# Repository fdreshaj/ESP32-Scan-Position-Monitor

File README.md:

Work in Progress, RF branch for RF. Will be updating with new design

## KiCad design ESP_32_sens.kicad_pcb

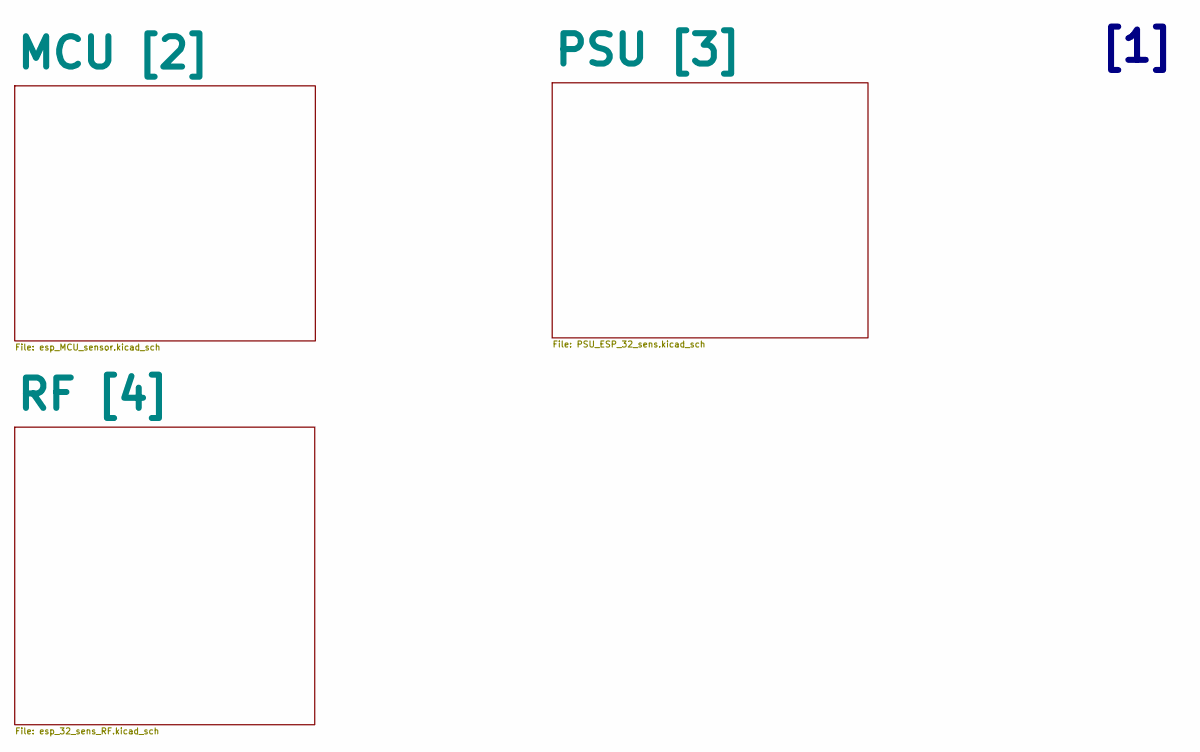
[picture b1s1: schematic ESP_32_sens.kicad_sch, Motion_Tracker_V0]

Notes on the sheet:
[1]

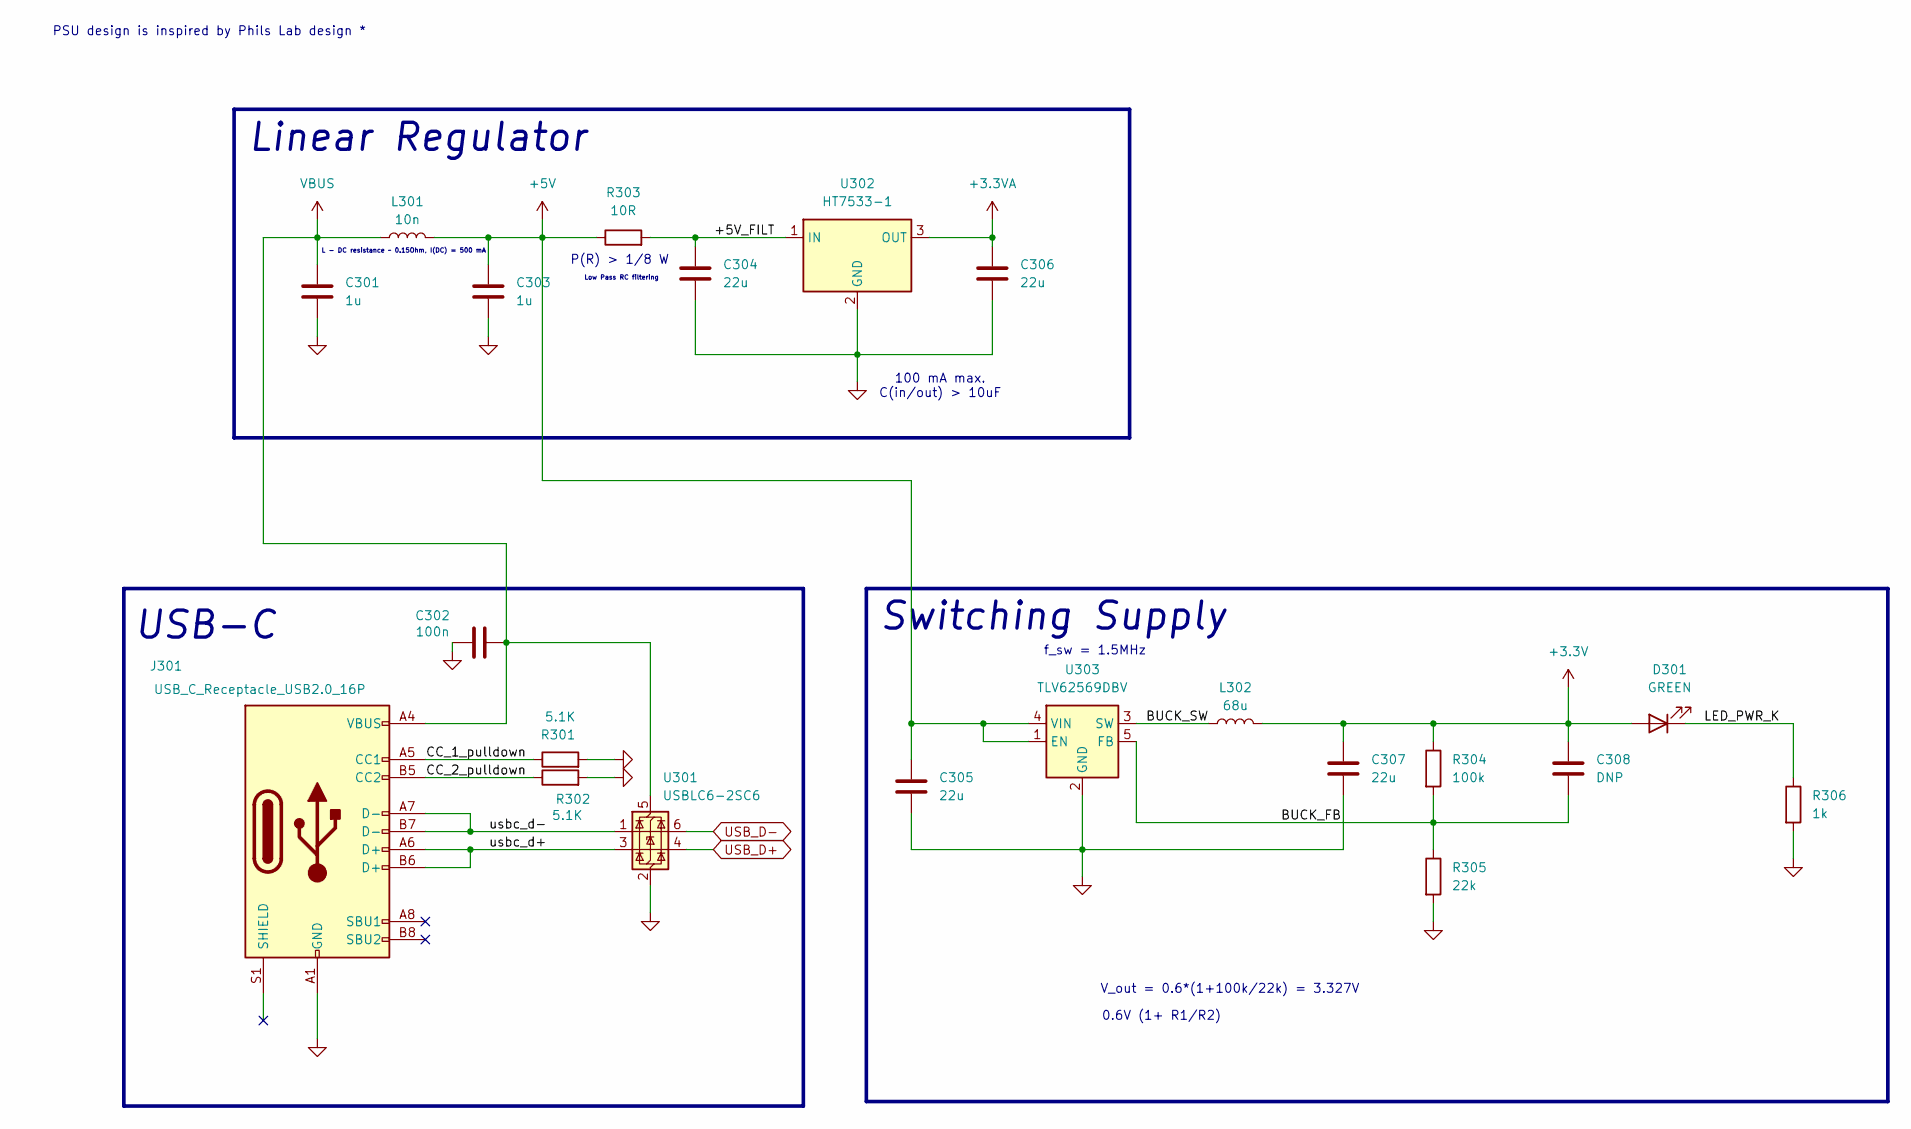
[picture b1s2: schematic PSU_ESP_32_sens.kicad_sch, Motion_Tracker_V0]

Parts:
C301, C303: 1u; C_0603_1608Metric_Pad1.08x0.95mm_HandSolder
C302: 100n; C_0402_1005Metric_Pad0.74x0.62mm_HandSolder
C304, C305, C306, C307: 22u; C_0603_1608Metric_Pad1.08x0.95mm_HandSolder
C308: DNP; C_0402_1005Metric_Pad0.74x0.62mm_HandSolder
D301: GREEN; LED_0402_1005Metric_Pad0.77x0.64mm_HandSolder
J301: USB_C_Receptacle_USB2.0_16P; USB_C_Receptacle_G-Switch_GT-USB-7010ASV
L301: 10n; L_0402_1005Metric_Pad0.77x0.64mm_HandSolder
L302: 68u; L_0603_1608Metric_Pad1.05x0.95mm_HandSolder
R301, R302: 5.1K; R_0402_1005Metric_Pad0.72x0.64mm_HandSolder
R303: 10R; R_0402_1005Metric_Pad0.72x0.64mm_HandSolder
R304: 100k; R_0402_1005Metric_Pad0.72x0.64mm_HandSolder
R305: 22k; R_0402_1005Metric_Pad0.72x0.64mm_HandSolder
R306: 1k; R_0402_1005Metric_Pad0.72x0.64mm_HandSolder
U301: USBLC6-2SC6; SOT-23-6
U302: HT7533-1; SOT-223-3_TabPin2
U303: TLV62569DBV; SOT-23-5

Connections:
+3.3V: C307.1, C308.1, D301.2 (A), L302.2, R304.1; also elsewhere on the board
+3.3VA: C306.1, U302.3 (OUT); also elsewhere on the board
+5V: C303.1, C305.1, L301.2, R303.1, U303.1 (EN), U303.4 (VIN)
/PSU [3]/+5V_FILT: C304.1, R303.2, U302.1 (IN)
/PSU [3]/BUCK_FB: C308.2, R304.2, R305.1, U303.5 (FB)
/PSU [3]/BUCK_SW: L302.1, U303.3 (SW)
/PSU [3]/CC_1_pulldown: J301.A5 (CC1), R301.1
/PSU [3]/CC_2_pulldown: J301.B5 (CC2), R302.1
/PSU [3]/LED_PWR_K: D301.1 (K), R306.1
/PSU [3]/usbc_d+: J301.A6 (D+), J301.B6 (D+), U301.3 (I/O2)
/PSU [3]/usbc_d-: J301.A7 (D-), J301.B7 (D-), U301.1 (I/O1)
GND: C301.2, C302.1, C303.2, C304.2, C305.2, C306.2, C307.2, J301.A1 (GND), J301.A12 (GND), J301.B1 (GND), J301.B12 (GND), R301.2, R302.2, R305.2, R306.2, U301.2 (GND), U302.2 (GND), U303.2 (GND); also elsewhere on the board
USB_D+: U301.4 (I/O2); also elsewhere on the board
USB_D-: U301.6 (I/O1); also elsewhere on the board
VBUS: C301.1, C302.2, J301.A4 (VBUS), J301.A9 (VBUS), J301.B4 (VBUS), J301.B9 (VBUS), L301.1, U301.5 (VBUS)

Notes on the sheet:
USB-C
Linear Regulator
V_out = 0.6*(1+100k/22k) = 3.327V
Low Pass RC filtering
0.6V (1+ R1/R2)
f_sw = 1.5MHz
Switching Supply
L - DC resistance ~ 0.15Ohm, I(DC) = 500 mA
P(R) > 1/8 W
100 mA max. C(in/out) > 10uF
PSU design is inspired by Phils Lab design *

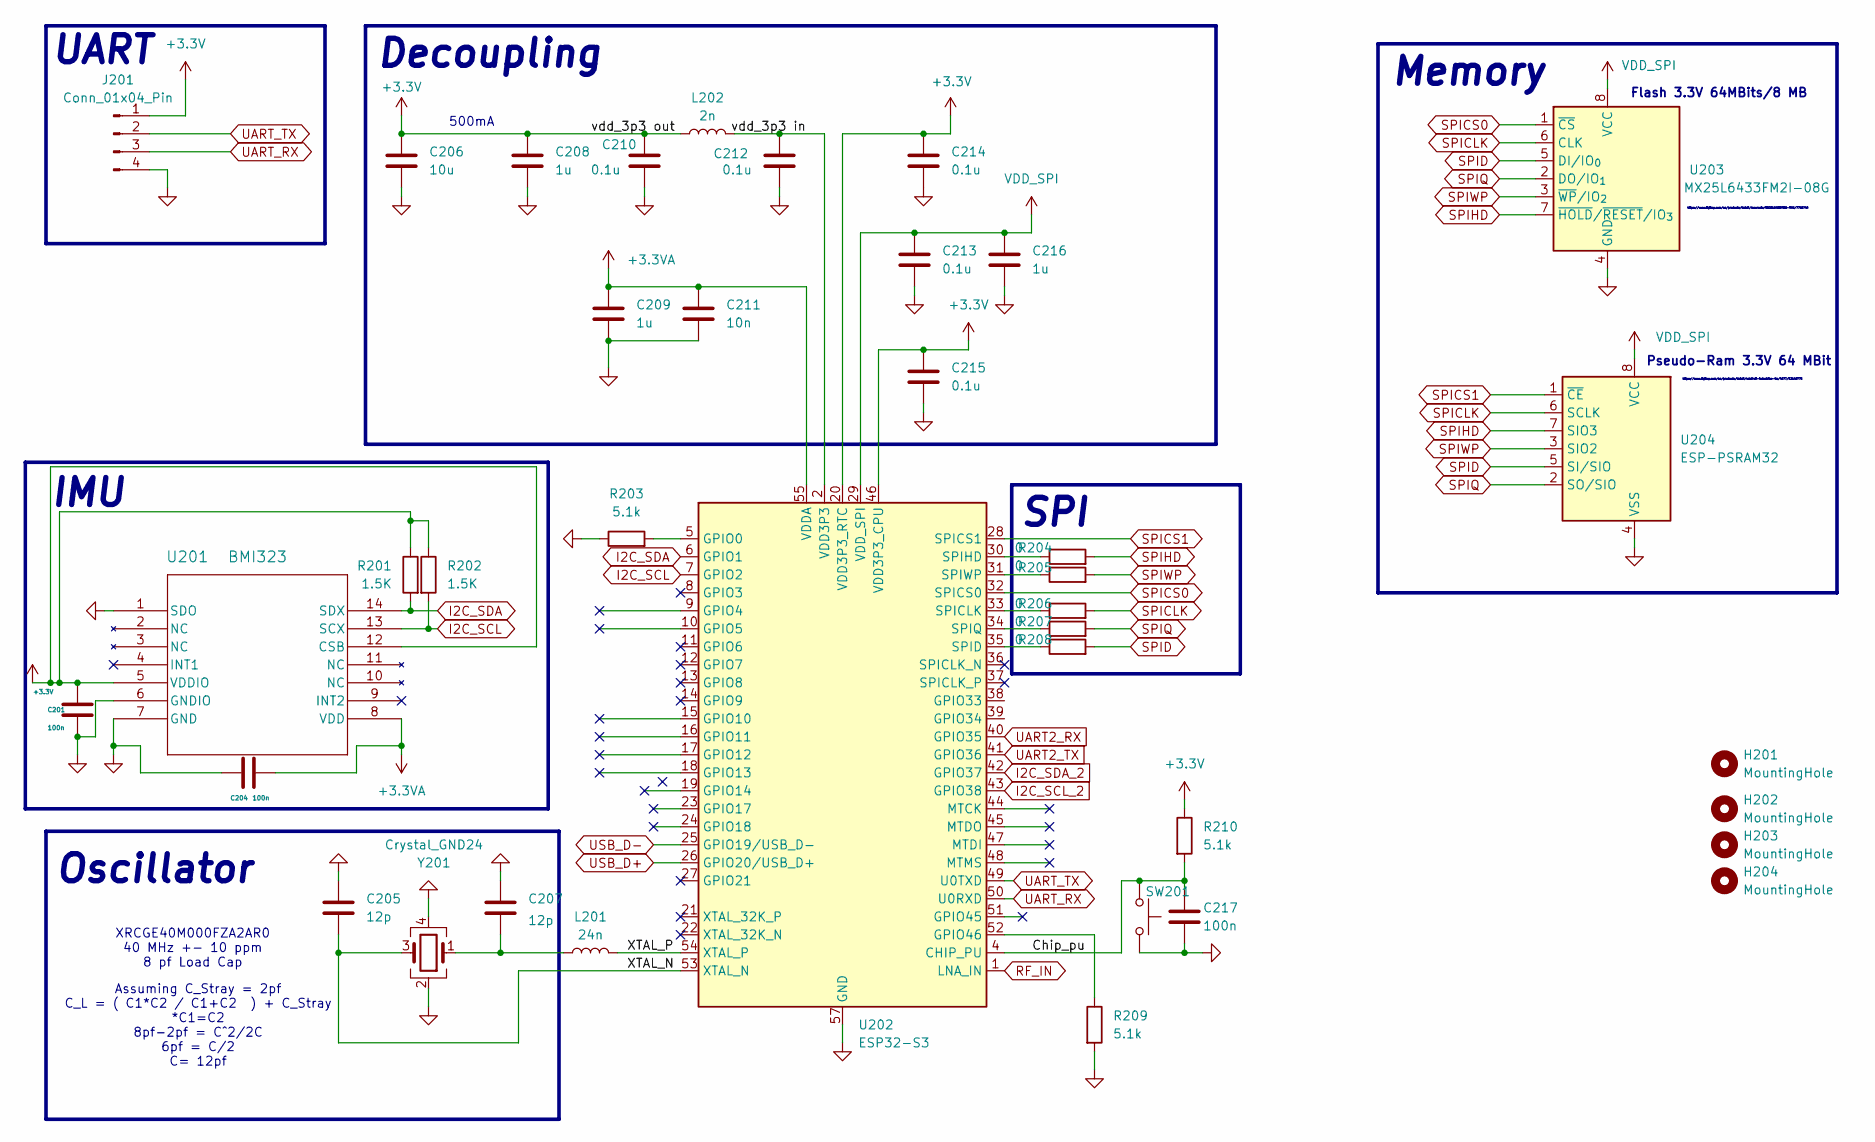
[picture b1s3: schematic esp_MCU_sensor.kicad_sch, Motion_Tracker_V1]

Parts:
C201, C204, C217: 100n; C_0402_1005Metric_Pad0.74x0.62mm_HandSolder
C205, C207: 12p; C_0402_1005Metric_Pad0.74x0.62mm_HandSolder
C206: 10u; C_0603_1608Metric_Pad1.08x0.95mm_HandSolder
C208, C209, C216: 1u; C_0603_1608Metric_Pad1.08x0.95mm_HandSolder
C210, C212, C213, C214, C215: 0.1u; C_0402_1005Metric_Pad0.74x0.62mm_HandSolder
C211: 10n; C_0402_1005Metric_Pad0.74x0.62mm_HandSolder
H201, H202, H203, H204: MountingHole; MountingHole_3.2mm_M3
J201: Conn_01x04_Pin; Wuerth_WR-WTB_64800411622_1x04_P1.50mm_Vertical
L201: 24n; L_0402_1005Metric_Pad0.77x0.64mm_HandSolder
L202: 2n; L_0402_1005Metric_Pad0.77x0.64mm_HandSolder
R201, R202: 1.5K; R_0402_1005Metric_Pad0.72x0.64mm_HandSolder
R203, R209, R210: 5.1k; R_0402_1005Metric_Pad0.72x0.64mm_HandSolder
R204, R205, R206, R207, R208: 0; R_0402_1005Metric_Pad0.72x0.64mm_HandSolder
SW201: SW_Push; SW_PUSH_6mm_H4.3mm
U201: BMI323; BMI323_BOS
U202: ESP32-S3; QFN-56-1EP_7x7mm_P0.4mm_EP4x4mm
U203: MX25L6433FM2I-08G; SOIC-8_5.3x5.3mm_P1.27mm
U204: ESP-PSRAM32; SOIC-8_3.9x4.9mm_P1.27mm
Y201: Crystal_GND24; Crystal_SMD_SeikoEpson_FA128-4Pin_2.0x1.6mm

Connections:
+3.3V: C201.1, C206.2, C208.2, C210.2, C214.1, C215.1, J201.1, L202.1, R201.1, R202.1, R210.1, U201.5 (VDDIO), U201.12 (CSB), U202.20 (VDD3P3_RTC), U202.46 (VDD3P3_CPU); also elsewhere on the board
+3.3VA: C204.2, C209.1, C211.1, U201.8 (VDD), U202.55 (VDDA), U202.56 (VDDA); also elsewhere on the board
/MCU [2]/Chip_pu: C217.1, R210.2, SW201.1, U202.4 (CHIP_PU)
/MCU [2]/XTAL_N: C205.1, U202.53 (XTAL_N), Y201.3
/MCU [2]/XTAL_P: L201.2, U202.54 (XTAL_P)
/MCU [2]/vdd_3p3 in: C212.2, L202.2, U202.2 (VDD3P3), U202.3 (VDD3P3)
GND: C201.2, C204.1, C205.2, C206.1, C207.2, C208.1, C209.2, C210.1, C211.2, C212.1, C213.2, C214.2, C215.2, C216.2, C217.2, J201.4, R203.1, R209.2, SW201.2, U201.1 (SDO), U201.6 (GNDIO), U201.7 (GND), U202.57 (GND), U203.4 (GND), U204.4 (VSS), Y201.2, Y201.4; also elsewhere on the board
I2C_SCL: R202.2, U201.13 (SCX), U202.7 (GPIO2)
I2C_SCL_2: U202.43 (GPIO38); also elsewhere on the board
I2C_SDA: R201.2, U201.14 (SDX), U202.6 (GPIO1)
I2C_SDA_2: U202.42 (GPIO37); also elsewhere on the board
unnamed: C207.1, L201.1, Y201.1
unnamed: R203.2, U202.5 (GPIO0)
unnamed: R209.1, U202.52 (GPIO46)
unnamed: R206.1, U202.33 (SPICLK)
unnamed: R208.1, U202.35 (SPID)
unnamed: R204.1, U202.30 (SPIHD)
unnamed: R207.1, U202.34 (SPIQ)
unnamed: R205.1, U202.31 (SPIWP)
RF_IN: U202.1 (LNA_IN); also elsewhere on the board
SPICLK: R206.2, U203.6 (CLK), U204.6 (SCLK)
SPICS0: U202.32 (SPICS0), U203.1 (~CS)
SPICS1: U202.28 (SPICS1), U204.1 (~CE)
SPID: R208.2, U203.5 (DI/IO_{0}), U204.5 (SI/SIO)
SPIHD: R204.2, U203.7 (~HOLD/~RESET/IO_{3}), U204.7 (SIO3)
SPIQ: R207.2, U203.2 (DO/IO_{1}), U204.2 (SO/SIO)
SPIWP: R205.2, U203.3 (~WP/IO_{2}), U204.3 (SIO2)
UART2_RX: U202.40 (GPIO35); also elsewhere on the board
UART2_TX: U202.41 (GPIO36); also elsewhere on the board
UART_RX: J201.3, U202.50 (U0RXD)
UART_TX: J201.2, U202.49 (U0TXD)
USB_D+: U202.26 (GPIO20/USB_D+); also elsewhere on the board
USB_D-: U202.25 (GPIO19/USB_D-); also elsewhere on the board
VDD_SPI: C213.1, C216.1, U202.29 (VDD_SPI), U203.8 (VCC), U204.8 (VCC)

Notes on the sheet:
SPI
IMU
Memory
Decoupling
UART
XRCGE40M000FZA2AR0 40 MHz +- 10 ppm 8 pf Load Cap
https://www.digikey.com/en/products/detail/adafruit-industries-llc/4677/13148775
Flash 3.3V 64MBits/8 MB
https://www.digikey.com/en/products/detail/macronix/MX25L6433FM2I-08G/7796740
500mA
Assuming C_Stray = 2pf C_L = ( C1*C2 / C1+C2 ) + C_Stray *C1=C2 8pf-2pf = C^2/2C 6pf = C/2 C= 12pf
Pseudo-Ram 3.3V 64 MBit
Oscillator

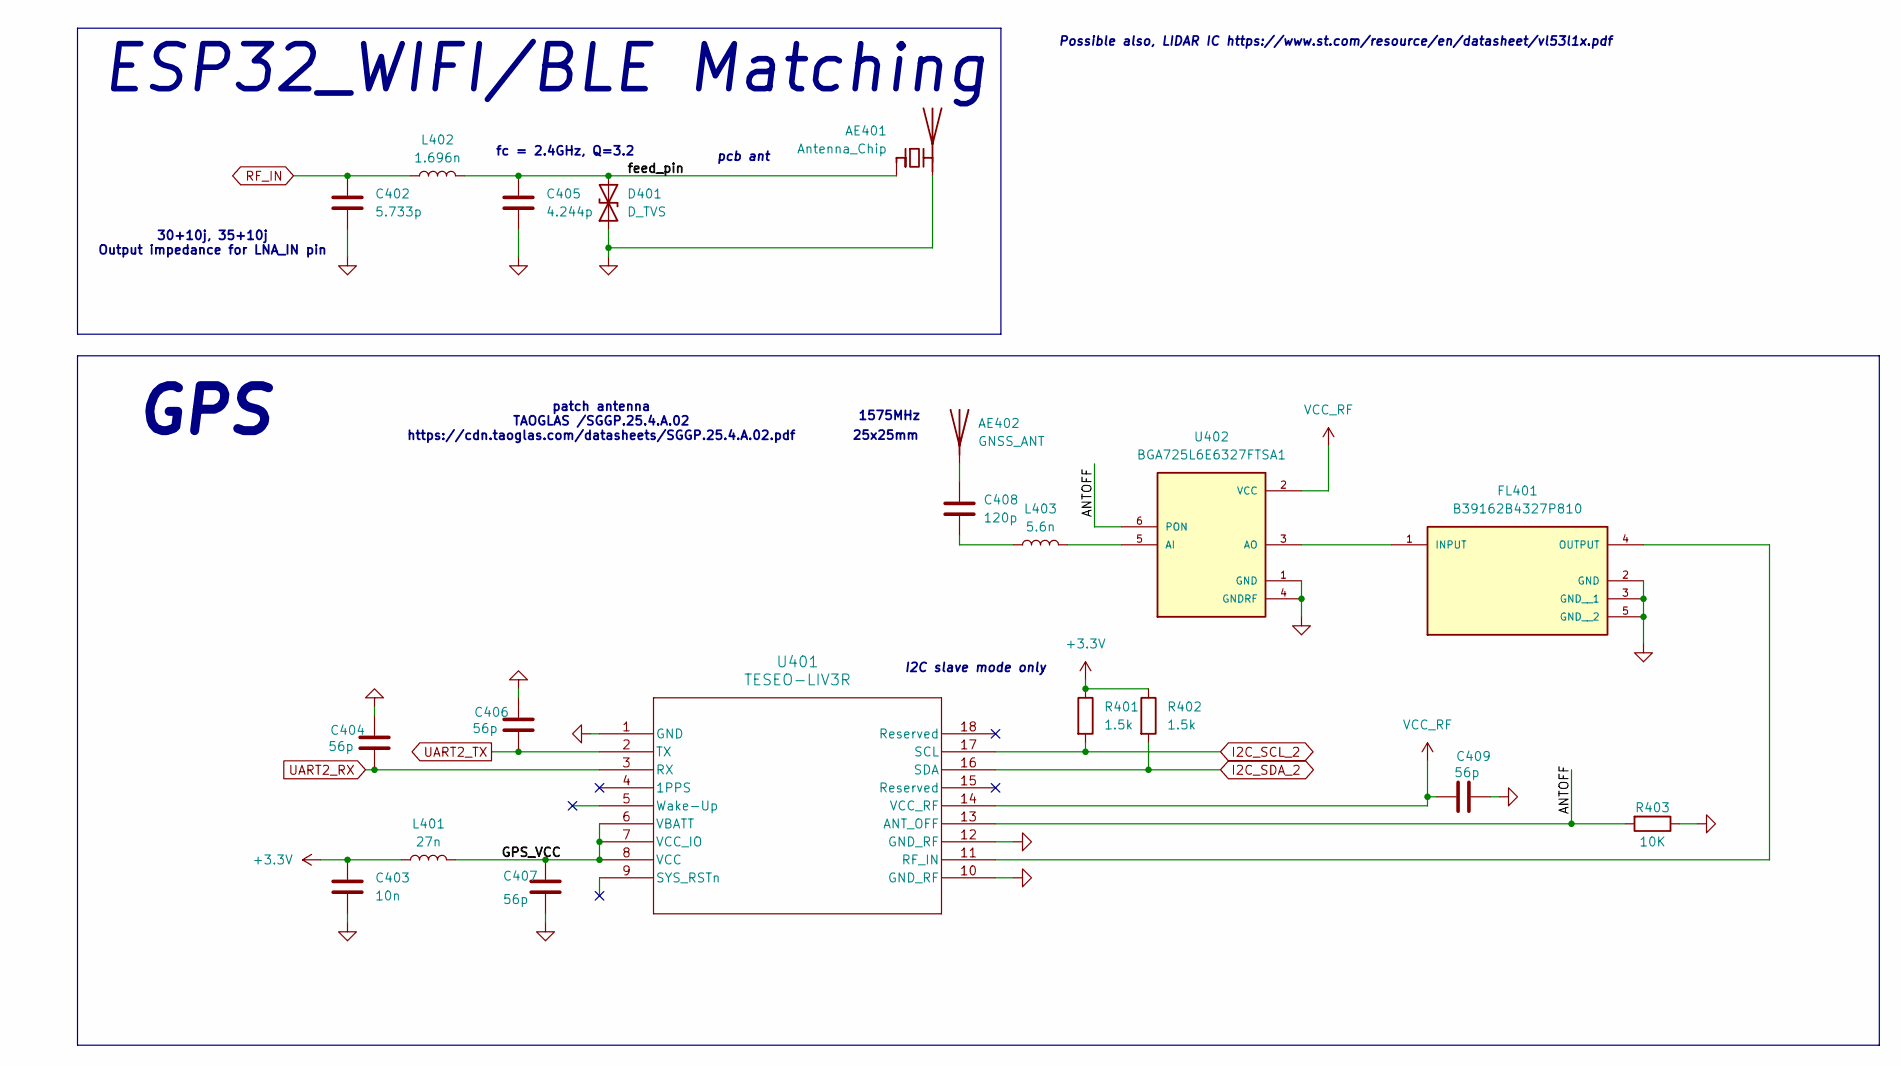
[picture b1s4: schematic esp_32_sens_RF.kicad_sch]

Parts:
AE401: Antenna_Chip; IFA_2.45_TI
AE402: GNSS_ANT; SGGP.25.4.A.02_TAL
C402: 5.733p; C_0201_0603Metric_Pad0.64x0.40mm_HandSolder
C403: 10n; C_0402_1005Metric_Pad0.74x0.62mm_HandSolder
C404, C406, C407, C409: 56p; C_0402_1005Metric_Pad0.74x0.62mm_HandSolder
C405: 4.244p; C_0201_0603Metric_Pad0.64x0.40mm_HandSolder
C408: 120p; C_0402_1005Metric_Pad0.74x0.62mm_HandSolder
D401: D_TVS; D_0402_1005Metric_Pad0.77x0.64mm_HandSolder
FL401: B39162B4327P810; FIL_B39162B4327P810; PARTREV October 25, 2019
L401: 27n; L_0402_1005Metric_Pad0.77x0.64mm_HandSolder
L402: 1.696n; L_0201_0603Metric_Pad0.64x0.40mm_HandSolder
L403: 5.6n; L_0402_1005Metric_Pad0.77x0.64mm_HandSolder
R401, R402: 1.5k; R_0402_1005Metric_Pad0.72x0.64mm_HandSolder
R403: 10K; R_0402_1005Metric_Pad0.72x0.64mm_HandSolder
U401: TESEO-LIV3R; ARRAY_LIV3R_STM
U402: BGA725L6E6327FTSA1; AMP_BGA725L6E6327FTSA1; PARTREV 2.0

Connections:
+3.3V: C403.1, L401.1, R401.1, R402.1; also elsewhere on the board
/RF [4]/ANTOFF: R403.2, U401.13 (ANT_OFF), U402.6 (PON)
/RF [4]/GPS_VCC: C407.1, L401.2, U401.6 (VBATT), U401.7 (VCC_IO), U401.8 (VCC)
/RF [4]/feed_pin: AE401.1 (FEED), C405.1, D401.2 (A2), L402.2
GND: AE401.2 (PCB_Trace), C402.2, C403.2, C404.1, C405.2, C406.1, C407.2, C409.1, D401.1 (A1), FL401.2 (GND), FL401.3 (GND__1), FL401.5 (GND__2), R403.1, U401.1 (GND), U401.10 (GND_RF), U401.12 (GND_RF), U402.1 (GND), U402.4 (GNDRF); also elsewhere on the board
I2C_SCL_2: R401.2, U401.17 (SCL); also elsewhere on the board
I2C_SDA_2: R402.2, U401.16 (SDA); also elsewhere on the board
unnamed: AE402.1 (A), C408.1
unnamed: C408.2, L403.1
unnamed: FL401.1 (INPUT), U402.3 (AO)
unnamed: FL401.4 (OUTPUT), U401.11 (RF_IN)
unnamed: L403.2, U402.5 (AI)
RF_IN: C402.1, L402.1; also elsewhere on the board
UART2_RX: C404.2, U401.3 (RX); also elsewhere on the board
UART2_TX: C406.2, U401.2 (TX); also elsewhere on the board
VCC_RF: C409.2, U401.14 (VCC_RF), U402.2 (VCC)

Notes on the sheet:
GPS
I2C slave mode only
pcb ant
Possible also, LIDAR IC https://www.st.com/resource/en/datasheet/vl53l1x.pdf
25x25mm
patch antenna TAOGLAS /SGGP.25.4.A.02 https://cdn.taoglas.com/datasheets/SGGP.25.4.A.02.pdf
30+10j, 35+10j Output impedance for LNA_IN pin
ESP32_WIFI/BLE Matching
fc = 2.4GHz, Q=3.2
1575MHz

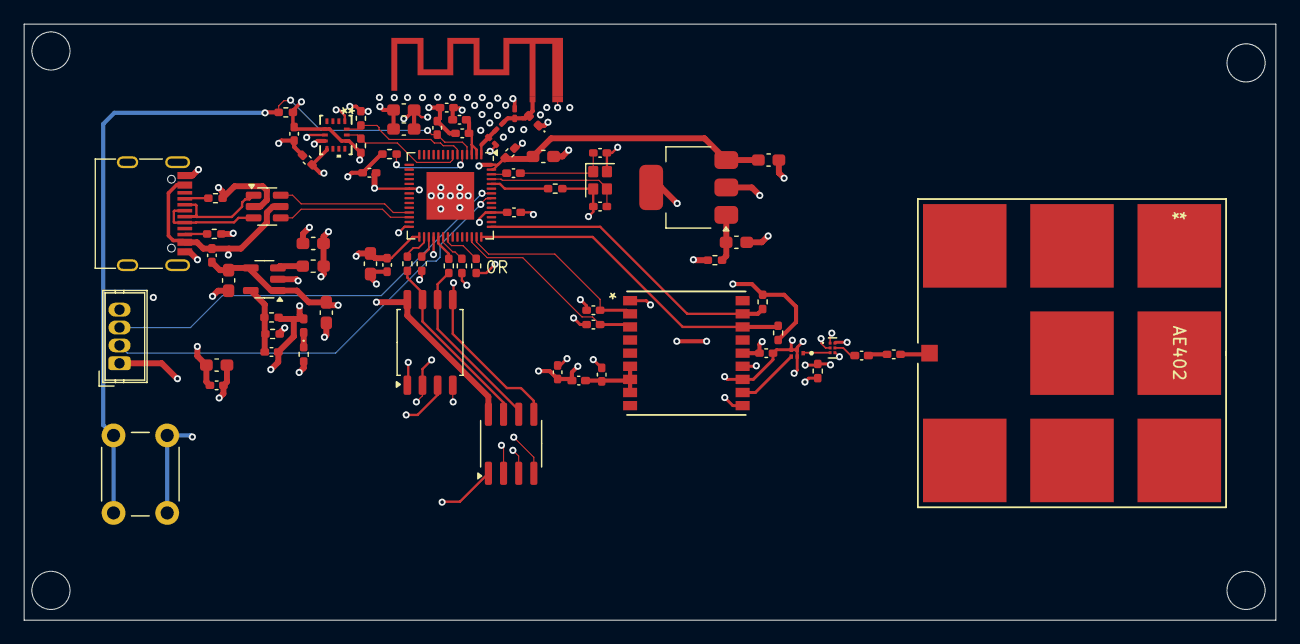
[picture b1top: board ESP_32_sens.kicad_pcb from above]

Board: 4 copper layers, 105.0 x 50.0 mm, 79 parts (0 on the bottom side), 53 nets.

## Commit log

2025-08-14 sent to folder grb
    sent to folder grb
2025-08-14 lck files
    lck fiels
2025-08-15 more correct ground plane
    ground plane
2025-08-15 additional comment
    additional comment
2025-08-18 Add RF schematics for GPS + designed Pi filter for imp matching
    added impedance matching on LNA 1 pin, added GPS/GNSS IC
2025-08-18 Added antenna design
    added pcb antenna design
2025-08-19 placement done
    placement done, routing left
2025-08-21 added via stichitching and routing,
    routing mostly done, Only power left
2025-08-22 finished power routing
    finished power routing, gps antenna left
2025-08-22 minor changes
    minor changes
2025-09-08 changes
    changes made
